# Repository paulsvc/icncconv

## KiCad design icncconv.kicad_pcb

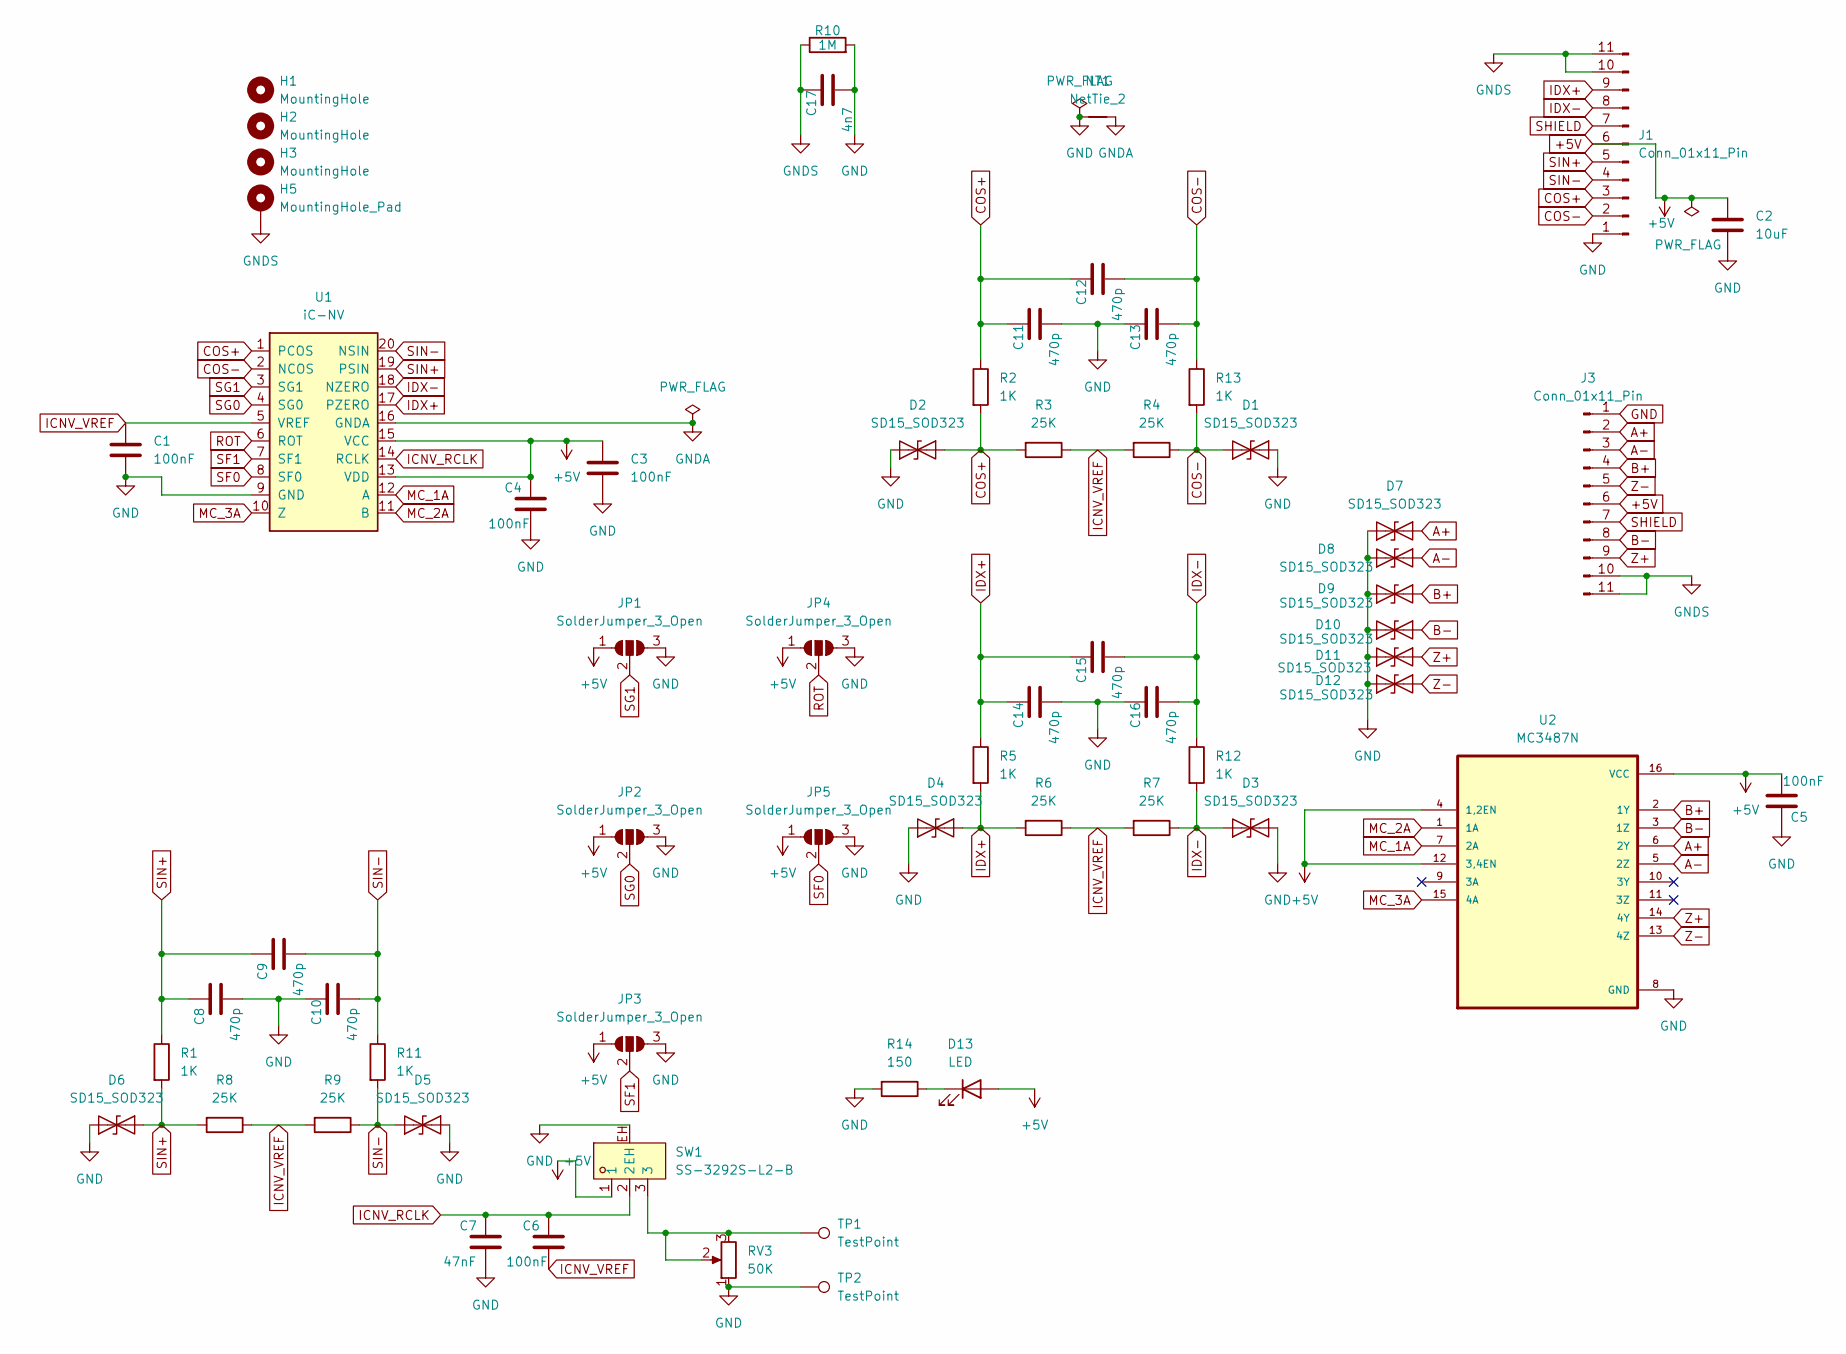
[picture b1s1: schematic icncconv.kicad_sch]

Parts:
C1, C3, C4, C5, C6: 100nF; C_0603_1608Metric_Pad1.08x0.95mm_HandSolder
C2: 10uF; C_0603_1608Metric_Pad1.08x0.95mm_HandSolder
C7: 47nF; C_0603_1608Metric_Pad1.08x0.95mm_HandSolder
C8, C9, C10, C11, C12, C13, C14, C15, C16: 470p; C_0603_1608Metric_Pad1.08x0.95mm_HandSolder
C17: 4n7; C_0603_1608Metric_Pad1.08x0.95mm_HandSolder
D1, D2, D3, D4, D5, D6, D7, D8, D9, D10, D11, D12: SD15_SOD323; D_SOD-323
D13: LED; LED-SMD_L3.2-W1.0-R-RD_GREEN
H1, H2, H3: MountingHole; MountingHole_3.2mm_M3
H5: MountingHole_Pad; MountingHole_3.2mm_M3_Pad
J1, J3: Conn_01x11_Pin; DB9-TH_D-SUB-DR-9PCM-CB
JP1, JP2, JP3, JP4, JP5: SolderJumper_3_Open; SolderJumper-3_P1.3mm_Open_Pad1.0x1.5mm
NT1: NetTie_2; NetTie-2_SMD_Pad2.0mm
R1, R2, R5, R11, R12, R13: 1K; R_0603_1608Metric_Pad0.98x0.95mm_HandSolder
R3, R4, R6, R7, R8, R9: 25K; R_0603_1608Metric_Pad0.98x0.95mm_HandSolder
R10: 1M; R_0603_1608Metric_Pad0.98x0.95mm_HandSolder
R14: 150; R_0603_1608Metric_Pad0.98x0.95mm_HandSolder
RV3: 50K; RES-ADJ-SMD_TC33X-2-104E
SW1: SS-3292S-L2-B; SW-SMD_SS-3292S-L2-B; LCSC Part C500057
TP1, TP2: TestPoint; Pin_D1.3mm_L11.0mm
U1: iC-NV; TSSOP-20_4.4x6.5mm_P0.65mm
U2: MC3487N; SOIC-16_L9.9-W3.9-P1.27-LS6.0-BL

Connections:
+5V: C2.1, C3.1, C4.1, C5.2, D13.2 (A), J1.6, J3.6, JP1.1 (A), JP2.1 (A), JP3.1 (A), JP4.1 (A), JP5.1 (A), SW1.1, U1.13 (VDD), U1.15 (VCC), U2.4 (1,2EN), U2.12 (3,4EN), U2.16 (VCC)
A+: D7.2 (A2), J3.2, U2.6 (2Y)
A-: D8.2 (A2), J3.3, U2.5 (2Z)
B+: D9.2 (A2), J3.4, U2.2 (1Y)
B-: D10.2 (A2), J3.8, U2.3 (1Z)
COS+: C11.1, C12.1, D2.2 (A2), J1.3, R2.1, R2.2, R3.2, U1.1 (PCOS)
COS-: C12.2, C13.2, D1.1 (A1), J1.2, R4.1, R13.1, R13.2, U1.2 (NCOS)
GND: C1.2, C2.2, C3.2, C4.2, C5.1, C7.2, C8.2, C10.1, C11.2, C13.1, C14.2, C16.1, C17.2, D1.2 (A2), D2.1 (A1), D3.2 (A2), D4.1 (A1), D5.2 (A2), D6.1 (A1), D7.1 (A1), D8.1 (A1), D9.1 (A1), D10.1 (A1), D11.1 (A1), D12.1 (A1), J1.1, J3.1, JP1.3 (B), JP2.3 (B), JP3.3 (B), JP4.3 (B), JP5.3 (B), NT1.1, R10.2, R14.2, RV3.1, SW1.EH, TP2.1, U1.9 (GND), U2.8 (GND)
GNDA: NT1.2, U1.16 (GNDA)
GNDS: C17.1, H5.1, J1.10, J1.11, J3.10, J3.11, R10.1
ICNV_RCLK: C6.1, C7.1, SW1.2, U1.14 (RCLK)
ICNV_VREF: C1.1, C6.2, R3.1, R4.2, R6.1, R7.2, R8.1, R9.2, U1.5 (VREF)
IDX+: C14.1, C15.1, D4.2 (A2), J1.9, R5.1, R5.2, R6.2, U1.17 (PZERO)
IDX-: C15.2, C16.2, D3.1 (A1), J1.8, R7.1, R12.1, R12.2, U1.18 (NZERO)
MC_1A: U1.12 (A), U2.7 (2A)
MC_2A: U1.11 (B), U2.1 (1A)
MC_3A: U1.10 (Z), U2.15 (4A)
unnamed: D13.1 (K), R14.1
unnamed: RV3.2, RV3.3, SW1.3, TP1.1
ROT: JP4.2 (C), U1.6 (ROT)
SF0: JP5.2 (C), U1.8 (SF0)
SF1: JP3.2 (C), U1.7 (SF1)
SG0: JP2.2 (C), U1.4 (SG0)
SG1: JP1.2 (C), U1.3 (SG1)
SHIELD: J1.7, J3.7
SIN+: C8.1, C9.1, D6.2 (A2), J1.5, R1.1, R1.2, R8.2, U1.19 (PSIN)
SIN-: C9.2, C10.2, D5.1 (A1), J1.4, R9.1, R11.1, R11.2, U1.20 (NSIN)
Z+: D11.2 (A2), J3.9, U2.14 (4Y)
Z-: D12.2 (A2), J3.5, U2.13 (4Z)

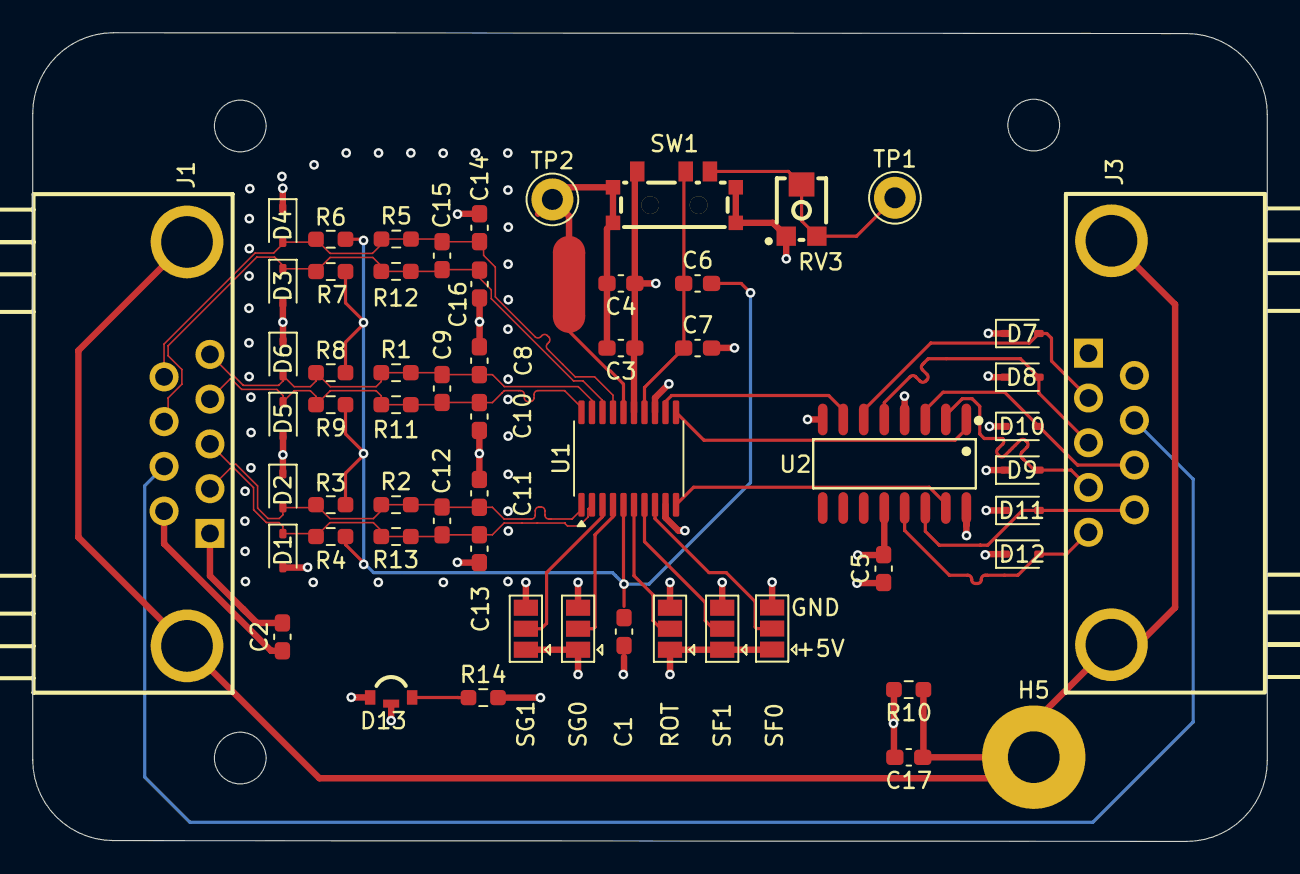
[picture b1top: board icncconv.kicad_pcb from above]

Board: 4 copper layers, 76.4 x 50.1 mm, 62 parts (0 on the bottom side), 29 nets.

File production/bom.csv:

Designator,Footprint,Quantity,Value,LCSC Part #
"C1, C3, C4, C5, C6",1206,5,100nF,C24497
"C10, C11, C12, C13, C14, C15, C16, C8, C9",1206,9,470p,C1868
C17,1206,1,4n7,C9192
C2,1206,1,10uF,C9807
C7,1206,1,47nF,C21812
"D1, D10, D11, D12, D2, D3, D4, D5, D6, D7, D8, D9",D_SOD-323,12,SD15_SOD323,C2931147
J1,DB9-TH_D-SUB-DR-9PCM-CB,1,Conn_01x11_Pin,C19077337
J3,DB9-TH_D-SUB-DR-9PCM-CB,1,Conn_01x11_Pin,C19077344
"R1, R11, R12, R13, R2, R5",1206,6,1K,C4410
R10,1206,1,1M,C393098
"R3, R4, R8, R9",1206,4,25K,C870587
"R6, R7",1206,2,25K,
RV3,RES-ADJ-SMD_TC33X-2-104E,1,50K,C913246
SW1,SW-SMD_SS-3292S-L2-B,1,SS-3292S-L2-B,C500057
"TP1, TP2",Pin_D1.3mm_L11.0mm,2,TestPoint,
U1,TSSOP-20_4.4x6.5mm_P0.65mm,1,iC-NV,C5240841
U2,SOIC-16_L9.9-W3.9-P1.27-LS6.0-BL,1,MC3487N,C2671192

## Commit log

2026-01-28 up EMI
2026-02-04 update prodv1
